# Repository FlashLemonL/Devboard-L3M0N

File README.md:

# Devboard-L3M0N
My attempt at making a devboard using the tutorial for when i want to start making IoT projects.

# 3D Model of PCB
Front 

Back

# BOM

# Parts Position

# PCB
Schematic            |  PCB         |
:-------------------------:|:-------------------------:|
    |    |

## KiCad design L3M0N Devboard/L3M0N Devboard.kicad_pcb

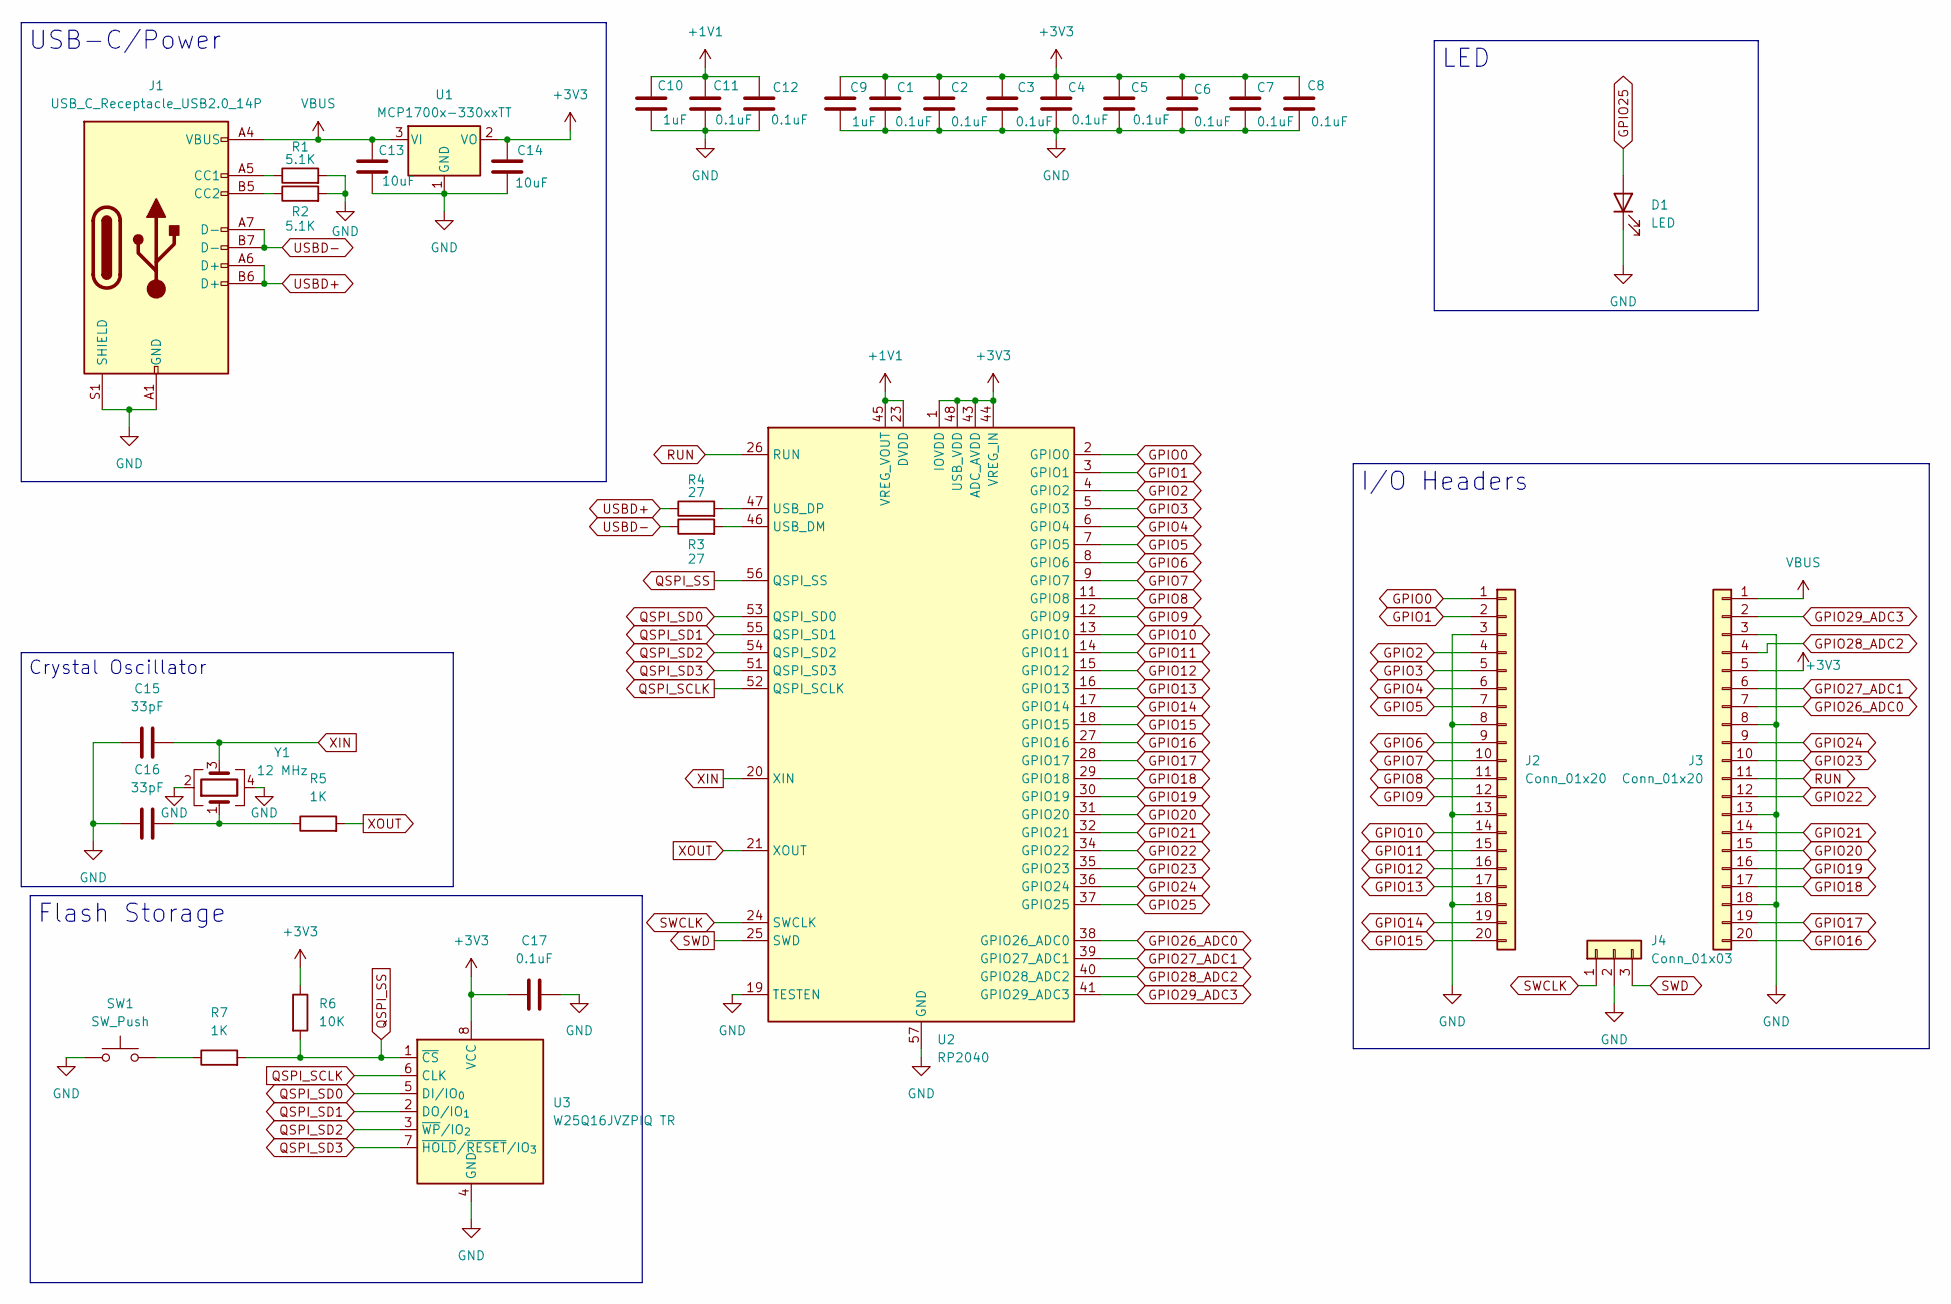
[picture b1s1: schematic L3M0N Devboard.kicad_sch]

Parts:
C1, C2, C3, C4, C5, C6, C7, C8, C11, C12, C17: 0.1uF; C_0402_1005Metric
C9, C10: 1uF; C_0402_1005Metric
C13, C14: 10uF; C_0603_1608Metric
C15, C16: 33pF; C_0402_1005Metric
D1: LED; LED_0603_1608Metric_Pad1.05x0.95mm_HandSolder
J1: USB_C_Receptacle_USB2.0_14P; USB_C_Receptacle_HRO_TYPE-C-31-M-12
J2, J3: Conn_01x20; PinHeader_1x20_P2.54mm_Vertical
J4: Conn_01x03; PinHeader_1x03_P2.54mm_Vertical
R1, R2: 5.1K; R_0402_1005Metric
R3, R4: 27; R_0402_1005Metric
R5, R7: 1K; R_0402_1005Metric
R6: 10K; R_0402_1005Metric
SW1: SW_Push; SW_Push_SPST_NO_Alps_SKRK
U1: MCP1700x-330xxTT; SOT-23
U2: RP2040; QFN-56-1EP_7x7mm_P0.4mm_EP3.2x3.2mm
U3: W25Q16JVZPIQ TR; Winbond_USON-8-1EP_3x2mm_P0.5mm_EP0.2x1.6mm
Y1: 12 MHz; Crystal_SMD_3225-4Pin_3.2x2.5mm

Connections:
+1V1: C10.1, C11.1, C12.1, U2.23 (DVDD), U2.45 (VREG_VOUT), U2.50 (DVDD)
+3V3: C1.1, C2.1, C3.1, C4.1, C5.1, C6.1, C7.1, C8.1, C9.1, C14.1, C17.1, J3.5, R6.1, U1.2 (VO), U2.1 (IOVDD), U2.10 (IOVDD), U2.22 (IOVDD), U2.33 (IOVDD), U2.42 (IOVDD), U2.43 (ADC_AVDD), U2.44 (VREG_IN), U2.48 (USB_VDD), U2.49 (IOVDD), U3.8 (VCC)
GND: C1.2, C2.2, C3.2, C4.2, C5.2, C6.2, C7.2, C8.2, C9.2, C10.2, C11.2, C12.2, C13.2, C14.2, C15.2, C16.1, C17.2, D1.1 (K), J1.A1 (GND), J1.A12 (GND), J1.B1 (GND), J1.B12 (GND), J1.S1 (SHIELD), J2.3, J2.8, J2.13, J2.18, J3.3, J3.8, J3.13, J3.18, J4.2, R1.2, R2.2, SW1.1, U1.1 (GND), U2.19 (TESTEN), U2.57 (GND), U3.4 (GND), Y1.2, Y1.4
GPIO0: J2.1, U2.2 (GPIO0)
GPIO1: J2.2, U2.3 (GPIO1)
GPIO2: J2.4, U2.4 (GPIO2)
GPIO3: J2.5, U2.5 (GPIO3)
GPIO4: J2.6, U2.6 (GPIO4)
GPIO5: J2.7, U2.7 (GPIO5)
GPIO6: J2.9, U2.8 (GPIO6)
GPIO7: J2.10, U2.9 (GPIO7)
GPIO8: J2.11, U2.11 (GPIO8)
GPIO9: J2.12, U2.12 (GPIO9)
GPIO10: J2.14, U2.13 (GPIO10)
GPIO11: J2.15, U2.14 (GPIO11)
GPIO12: J2.16, U2.15 (GPIO12)
GPIO13: J2.17, U2.16 (GPIO13)
GPIO14: J2.19, U2.17 (GPIO14)
GPIO15: J2.20, U2.18 (GPIO15)
GPIO16: J3.20, U2.27 (GPIO16)
GPIO17: J3.19, U2.28 (GPIO17)
GPIO18: J3.17, U2.29 (GPIO18)
GPIO19: J3.16, U2.30 (GPIO19)
GPIO20: J3.15, U2.31 (GPIO20)
GPIO21: J3.14, U2.32 (GPIO21)
GPIO22: J3.12, U2.34 (GPIO22)
GPIO23: J3.10, U2.35 (GPIO23)
GPIO24: J3.9, U2.36 (GPIO24)
GPIO25: D1.2 (A), U2.37 (GPIO25)
GPIO26_ADC0: J3.7, U2.38 (GPIO26_ADC0)
GPIO27_ADC1: J3.6, U2.39 (GPIO27_ADC1)
GPIO28_ADC2: J3.4, U2.40 (GPIO28_ADC2)
GPIO29_ADC3: J3.2, U2.41 (GPIO29_ADC3)
unnamed: C16.2, R5.1, Y1.1
unnamed: J1.A5 (CC1), R1.1
unnamed: J1.B5 (CC2), R2.1
unnamed: R7.1, SW1.2
unnamed: R3.2, U2.46 (USB_DM)
unnamed: R4.2, U2.47 (USB_DP)
QSPI_SCLK: U2.52 (QSPI_SCLK), U3.6 (CLK)
QSPI_SD0: U2.53 (QSPI_SD0), U3.5 (DI/IO_{0})
QSPI_SD1: U2.55 (QSPI_SD1), U3.2 (DO/IO_{1})
QSPI_SD2: U2.54 (QSPI_SD2), U3.3 (~WP/IO_{2})
QSPI_SD3: U2.51 (QSPI_SD3), U3.7 (~HOLD/~RESET/IO_{3})
QSPI_SS: R6.2, R7.2, U2.56 (QSPI_SS), U3.1 (~CS)
RUN: J3.11, U2.26 (RUN)
SWCLK: J4.1, U2.24 (SWCLK)
SWD: J4.3, U2.25 (SWD)
USBD+: J1.A6 (D+), J1.B6 (D+), R4.1
USBD-: J1.A7 (D-), J1.B7 (D-), R3.1
VBUS: C13.1, J1.A4 (VBUS), J1.A9 (VBUS), J1.B4 (VBUS), J1.B9 (VBUS), J3.1, U1.3 (VI)
XIN: C15.1, U2.20 (XIN), Y1.3
XOUT: R5.2, U2.21 (XOUT)

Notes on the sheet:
Flash Storage
USB-C/Power
I/O Headers
Crystal Oscillator
LED

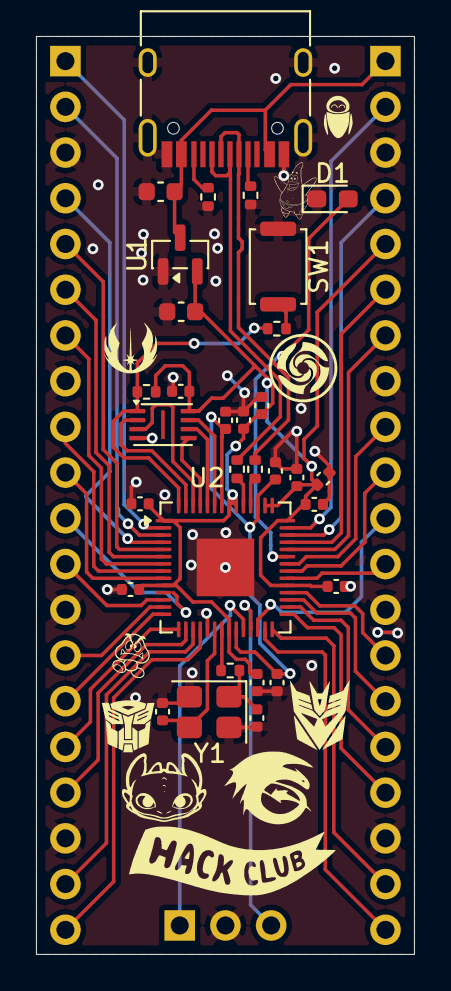
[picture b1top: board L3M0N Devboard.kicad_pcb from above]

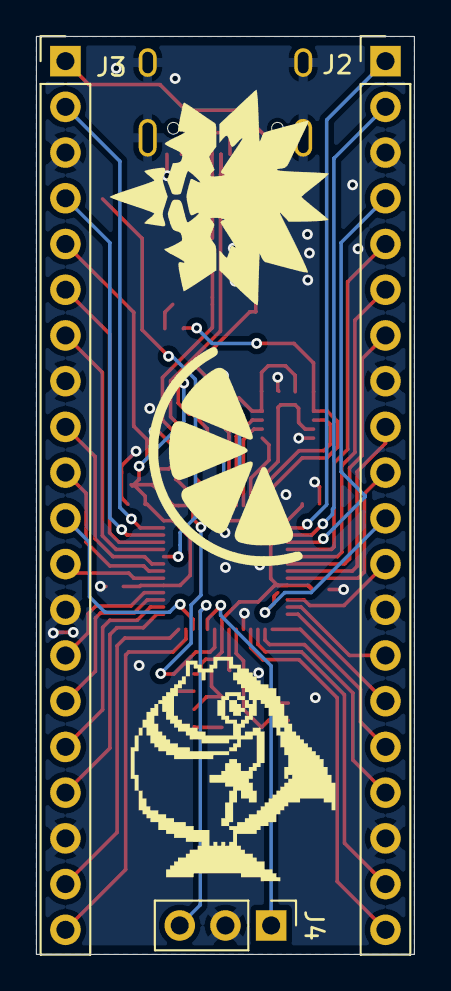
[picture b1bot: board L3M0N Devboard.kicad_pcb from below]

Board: 2 copper layers, 21.0 x 51.0 mm, 34 parts (3 on the bottom side), 53 nets.

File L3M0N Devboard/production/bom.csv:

Designator,Footprint,Quantity,Value,LCSC Part #
"C1, C11, C12, C17, C2, C3, C4, C5, C6, C7, C8",0402,11,0.1uF,
"C10, C9",0402,2,1uF,
"C13, C14",0603,2,10uF,
"C15, C16",0402,2,33pF,
J1,USB_C_Receptacle_HRO_TYPE-C-31-M-12,1,USB_C_Receptacle_USB2.0_14P,
"J2, J3",PinHeader_1x20_P2.54mm_Vertical,2,Conn_01x20,
J4,PinHeader_1x03_P2.54mm_Vertical,1,Conn_01x03,
"R1, R2",0402,2,5.1K,
"R3, R4",0402,2,27,
"R5, R7",0402,2,1K,
R6,0402,1,10K,
SW1,SW_Push_SPST_NO_Alps_SKRK,1,SW_Push,
U1,SOT-23,1,MCP1700x-330xxTT,
U2,QFN-56-1EP_7x7mm_P0.4mm_EP3.2x3.2mm,1,RP2040,
U3,Winbond_USON-8-1EP_3x2mm_P0.5mm_EP0.2x1.6mm,1,W25Q16JVZPIQ TR,
Y1,Crystal_SMD_3225-4Pin_3.2x2.5mm,1,12 MHz,

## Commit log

2025-12-22 Added RP2040 to schematic and power decoupling
2025-12-22 Added USB C receptacle
2025-12-22 Added crystal oscilator
2026-03-06 Assigned footrprints
2026-03-06 Started positioning parts for pcb
2026-03-09 started some of the wiring
2026-03-09 Wired up the left side of the devboard (Besides GND)
2026-03-09 added left wires and ground fill
2026-03-10 flipped the header pins
2026-03-10 fixed ground fill and silkscreen and added things to silkscreen
2026-03-11 made the gerber file
2026-03-12 Added Pictures for ReadMe
2026-03-22 Added LED and updated ReadMe
